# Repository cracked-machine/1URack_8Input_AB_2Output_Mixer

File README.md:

# 1URack_8Input_AB_2Output_Mixer
Eurorack-compatible 1U 8-channel mixer with selectable A/B outputs. 

<a href="https://www.instagram.com/p/BnoBRM4nUFm/?utm_source=ig_web_copy_link">Link to demo video!</a>

Assembly Instructions:
======================

A. Resistors

1) 8 x 2K2 on all R_LEDX positions (**R_LED1** - **R_LED8**)
2) 8 x 10K on all R_ChannelAB_OAin_RinX positions (**R_ChannelAB_OAin_Rin1** - **R_ChannelAB_OAin_Rin8**)
3) 2 x 10K on **R_ChanA_OAin_Rf1** and **R_ChanB_OAin_Rf1**
4) 2 x 22K on **R_ChanA_OAout_Rin1** and **R_ChanB_OAout_Rin1**
5) 2 x 1K  on **R_ChanA_OAout1** and **R_ChanB_OAout1** 

B. Capacitors

1) 2 x 100nF on **C_ChanA_POSBY1** and **C_ChanB_POSBY1**
2) 2 x 100nF on **C_ChanA_NEGBY1** and **C_ChanB_NEGBY1**
3) 1 x 100nF on **C_PW_BYNEG1**
4) 1 x 100nF on **C_PW_BYPOS1**

C. SOIC components

1) 2 x TL072 on **U_ChanA_OA1** and **U_ChanB_OA1**

D. ThroughHole Components

1) Solder one fader per section (1-8, A and B). Will only fit one way
2) Solder one Jack socket per section (1-8, A and B). Will only fit one way
3) solder one switch per input section (1-8). Orientation does not matter.
4) Solder pin headers in the power supply holes (2x5).

Troubleshooting:
================

1. Signal check:

Run a VCO signal into each of the inputs and check the signal at both outputs. You can use either an amplifier or an scope at the outputs. It can be helpful to draw a 2x8 grid for the inputs/outputs so you can mark each one in turn as you check.

If any of the inputs fail to produce a signal at an output then check that input section. If no signal appears at one of the output then check that output section. See below for further checks....

2. Visual Inspection:

Most problems will arise from bad solder joints on the SMT components so be sure to make a final visual inspection when done. 
You might find it easier to do this after cleaning the flux off the pcb first. If in doubt retouch the solder joint.

3. Electrical check:

Check for +/-12V voltages at the power supply pins. Also check pins 8 (positive) and 4 (negative) on the two SOIC TL072 OpAmps. 

Use a DMM to check the continuity between component pins.  

Check the resistance on pins connected to each resistor after soldering. If you get an open circuit reading then resolder the component.  Seeing a resistance value significantly less than marked, can be a sign that another component has bad solder joints.

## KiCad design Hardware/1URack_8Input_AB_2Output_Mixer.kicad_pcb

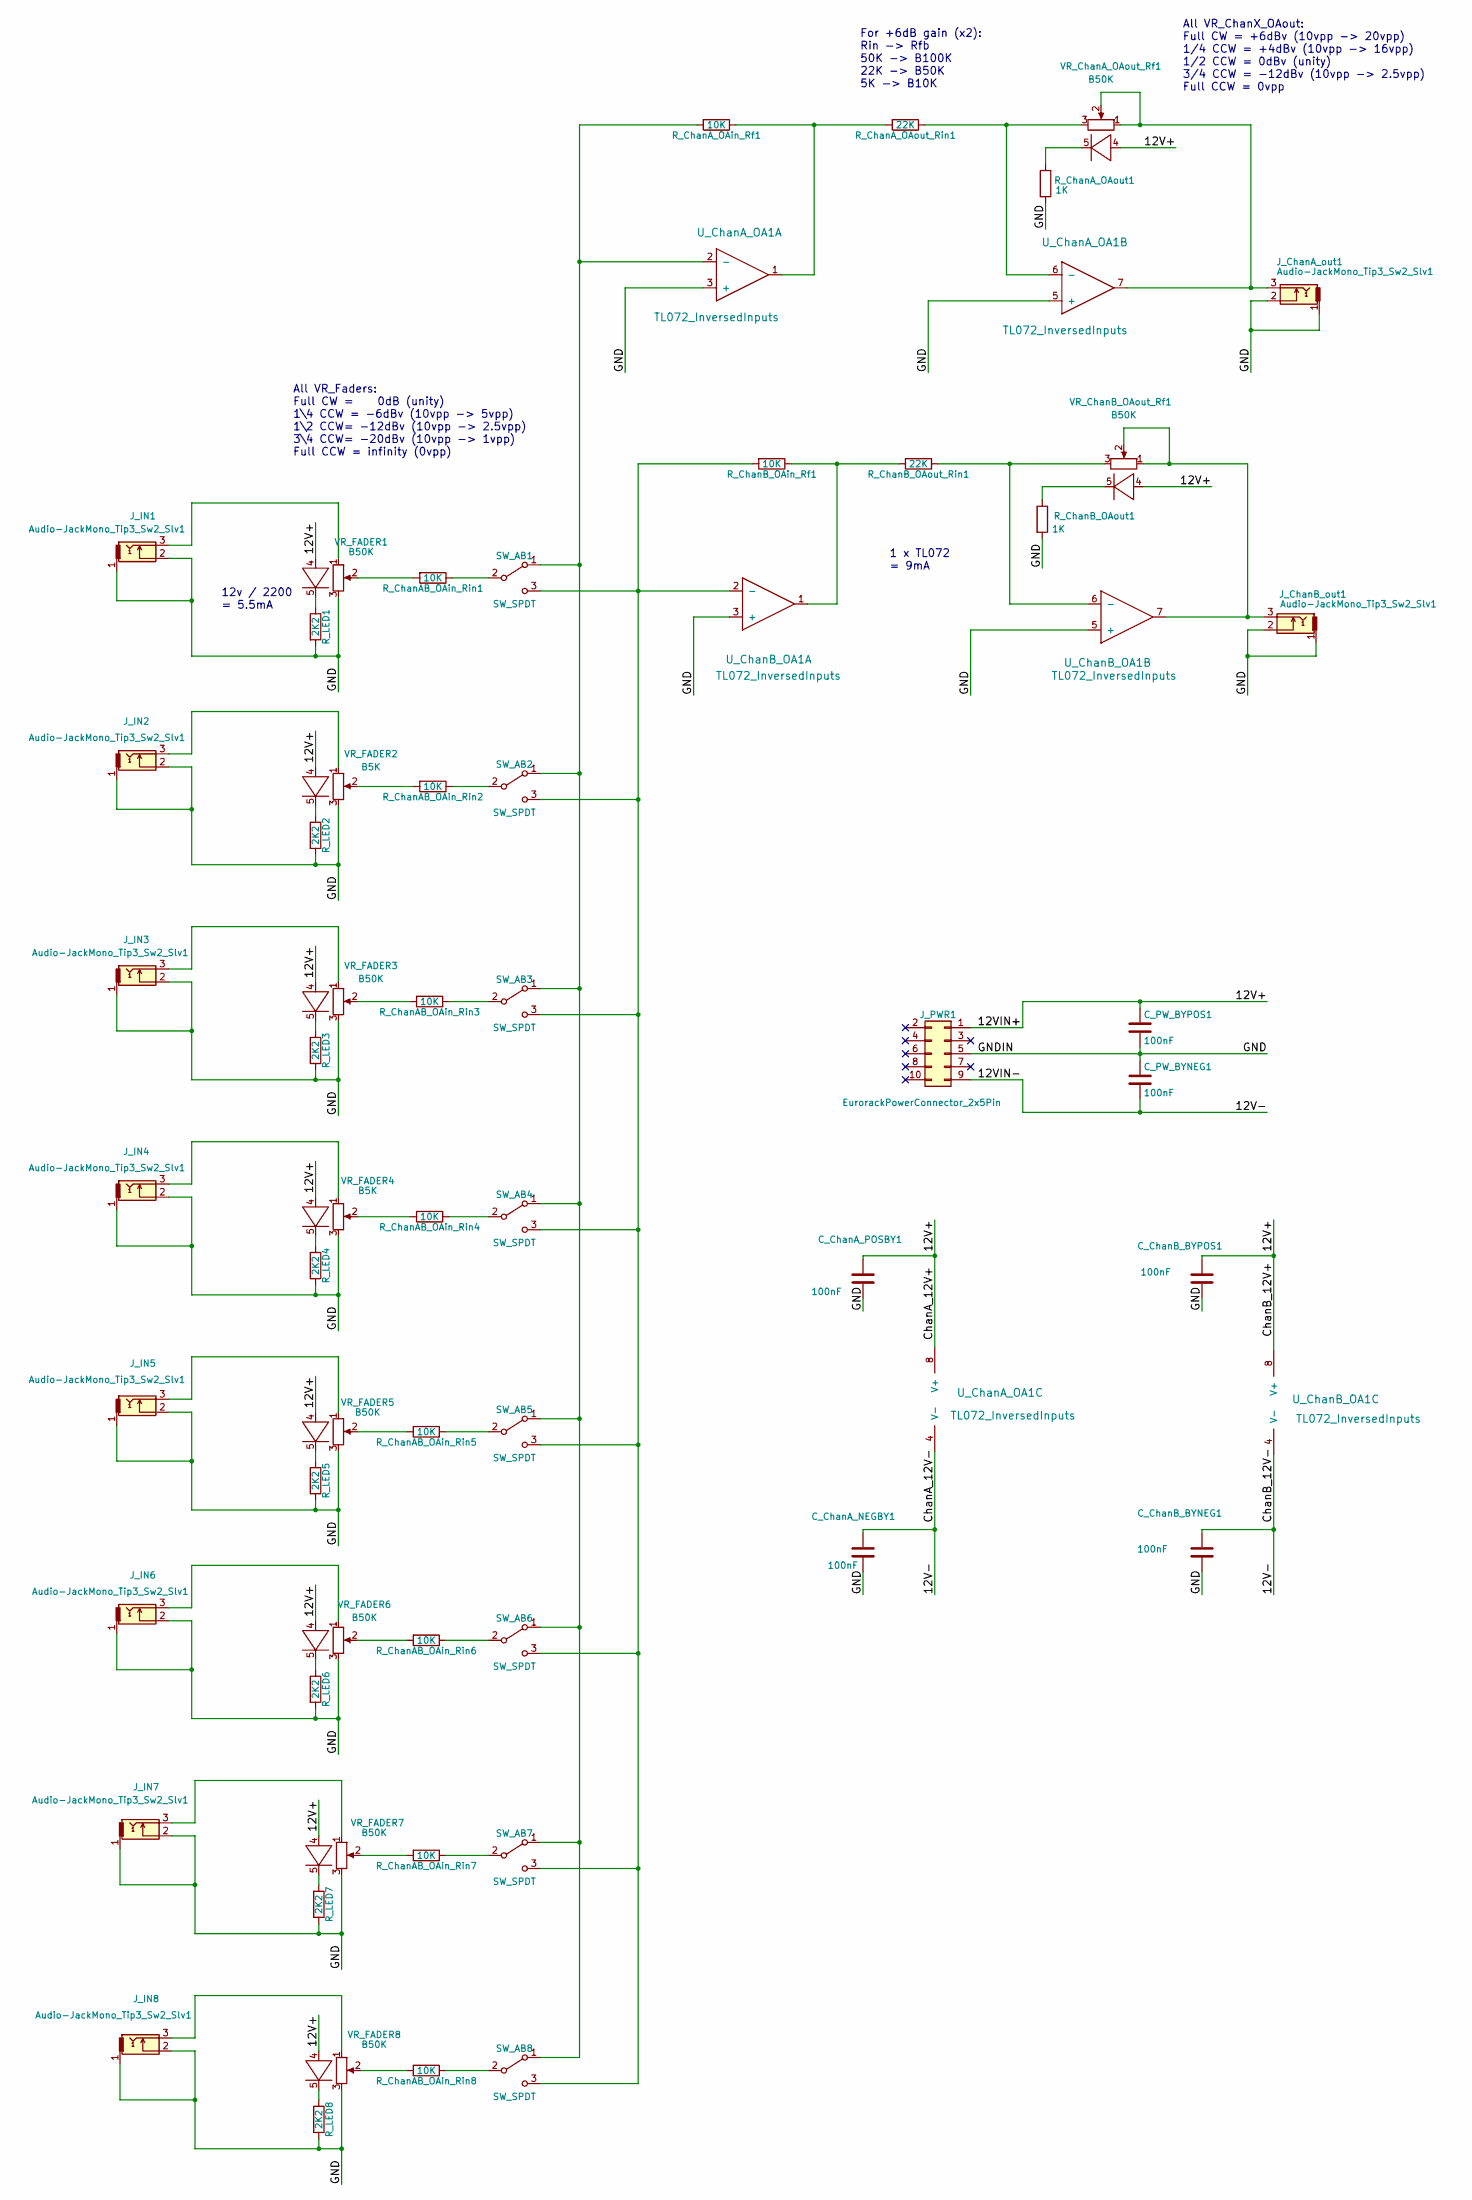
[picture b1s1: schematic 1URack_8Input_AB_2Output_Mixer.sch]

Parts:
C_ChanA_NEGBY1: 100nF; C_0805_HandSoldering
C_ChanA_POSBY1: 100nF; C_0805_HandSoldering
C_ChanB_BYNEG1: 100nF; C_0805_HandSoldering
C_ChanB_BYPOS1: 100nF; C_0805_HandSoldering
C_PW_BYNEG1: 100nF; C_0805_HandSoldering
C_PW_BYPOS1: 100nF; C_0805_HandSoldering
J_ChanA_out1: Audio-JackMono_Tip3_Sw2_Slv1; Conn_3.5mmJackMono_Vertical_PJ301M-12
J_ChanB_out1: Audio-JackMono_Tip3_Sw2_Slv1; Conn_3.5mmJackMono_Vertical_PJ301M-12
J_IN1, J_IN2, J_IN3, J_IN4, J_IN5, J_IN6, J_IN7, J_IN8: Audio-JackMono_Tip3_Sw2_Slv1; Conn_3.5mmJackMono_Vertical_PJ301M-12
J_PWR1: EurorackPowerConnector_2x5Pin; Pin_Header_Straight_2x05_Pitch2.54mm
R_ChanAB_OAin_Rin1, R_ChanAB_OAin_Rin2, R_ChanAB_OAin_Rin3, R_ChanAB_OAin_Rin4, R_ChanAB_OAin_Rin5, R_ChanAB_OAin_Rin6, R_ChanAB_OAin_Rin7, R_ChanAB_OAin_Rin8: 10K; R_0805_HandSoldering
R_ChanA_OAin_Rf1: 10K; R_0805_HandSoldering
R_ChanA_OAout1: 1K; R_0805_HandSoldering
R_ChanA_OAout_Rin1: 22K; R_0805_HandSoldering
R_ChanB_OAin_Rf1: 10K; R_0805_HandSoldering
R_ChanB_OAout1: 1K; R_0805_HandSoldering
R_ChanB_OAout_Rin1: 22K; R_0805_HandSoldering
R_LED1, R_LED2, R_LED3, R_LED4, R_LED5, R_LED6, R_LED7, R_LED8: 2K2; R_0805_HandSoldering
SW_AB1, SW_AB2, SW_AB3, SW_AB4, SW_AB5, SW_AB6, SW_AB7, SW_AB8: SW_SPDT; Dailywell_SPDT
U_ChanA_OA1: TL072_InversedInputs; SOIC-8-N
U_ChanB_OA1: TL072_InversedInputs; SOIC-8-N
VR_ChanA_OAout_Rf1: B50K; Slider_PTL20_LED_35MM
VR_ChanB_OAout_Rf1: B50K; Slider_PTL20_LED_35MM
VR_FADER1, VR_FADER3, VR_FADER5, VR_FADER6, VR_FADER7, VR_FADER8: B50K; Slider_PTL20_LED_35MM
VR_FADER2, VR_FADER4: B5K; Slider_PTL20_LED_35MM

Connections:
/12V+: C_ChanA_POSBY1.1, C_ChanB_BYPOS1.1, C_PW_BYPOS1.1, J_PWR1.1, U_ChanA_OA1.8 (V+), U_ChanB_OA1.8 (V+), VR_ChanA_OAout_Rf1.4, VR_ChanB_OAout_Rf1.4, VR_FADER1.4, VR_FADER2.4, VR_FADER3.4, VR_FADER4.4, VR_FADER5.4, VR_FADER6.4, VR_FADER7.4, VR_FADER8.4
/12V-: C_ChanA_NEGBY1.1, C_ChanB_BYNEG1.1, C_PW_BYNEG1.2, J_PWR1.9, U_ChanA_OA1.4 (V-), U_ChanB_OA1.4 (V-)
/GND: C_ChanA_NEGBY1.2, C_ChanA_POSBY1.2, C_ChanB_BYNEG1.2, C_ChanB_BYPOS1.2, C_PW_BYNEG1.1, C_PW_BYPOS1.2, J_ChanA_out1.1, J_ChanA_out1.2, J_ChanB_out1.1, J_ChanB_out1.2, J_IN1.1, J_IN1.2, J_IN2.1, J_IN2.2, J_IN3.1, J_IN3.2, J_IN4.1, J_IN4.2, J_IN5.1, J_IN5.2, J_IN6.1, J_IN6.2, J_IN7.1, J_IN7.2, J_IN8.1, J_IN8.2, J_PWR1.5, R_ChanA_OAout1.2, R_ChanB_OAout1.2, R_LED1.2, R_LED2.2, R_LED3.2, R_LED4.2, R_LED5.2, R_LED6.2, R_LED7.2, R_LED8.2, U_ChanA_OA1.3 (+), U_ChanA_OA1.5 (+), U_ChanB_OA1.3 (+), U_ChanB_OA1.5 (+), VR_FADER1.3, VR_FADER2.3, VR_FADER3.3, VR_FADER4.3, VR_FADER5.3, VR_FADER6.3, VR_FADER7.3, VR_FADER8.3
unnamed: J_ChanA_out1.3, U_ChanA_OA1.7, VR_ChanA_OAout_Rf1.1, VR_ChanA_OAout_Rf1.2
unnamed: J_ChanB_out1.3, U_ChanB_OA1.7, VR_ChanB_OAout_Rf1.1, VR_ChanB_OAout_Rf1.2
unnamed: J_IN1.3, VR_FADER1.1
unnamed: J_IN2.3, VR_FADER2.1
unnamed: J_IN3.3, VR_FADER3.1
unnamed: J_IN4.3, VR_FADER4.1
unnamed: J_IN5.3, VR_FADER5.1
unnamed: J_IN6.3, VR_FADER6.1
unnamed: J_IN7.3, VR_FADER7.1
unnamed: J_IN8.3, VR_FADER8.1
unnamed: R_ChanAB_OAin_Rin1.1, SW_AB1.2 (B)
unnamed: R_ChanAB_OAin_Rin1.2, VR_FADER1.2
unnamed: R_ChanAB_OAin_Rin2.1, SW_AB2.2 (B)
unnamed: R_ChanAB_OAin_Rin2.2, VR_FADER2.2
unnamed: R_ChanAB_OAin_Rin3.1, SW_AB3.2 (B)
unnamed: R_ChanAB_OAin_Rin3.2, VR_FADER3.2
unnamed: R_ChanAB_OAin_Rin4.1, SW_AB4.2 (B)
unnamed: R_ChanAB_OAin_Rin4.2, VR_FADER4.2
unnamed: R_ChanAB_OAin_Rin5.1, SW_AB5.2 (B)
unnamed: R_ChanAB_OAin_Rin5.2, VR_FADER5.2
unnamed: R_ChanAB_OAin_Rin6.1, SW_AB6.2 (B)
unnamed: R_ChanAB_OAin_Rin6.2, VR_FADER6.2
unnamed: R_ChanAB_OAin_Rin7.1, SW_AB7.2 (B)
unnamed: R_ChanAB_OAin_Rin7.2, VR_FADER7.2
unnamed: R_ChanAB_OAin_Rin8.1, SW_AB8.2 (B)
unnamed: R_ChanAB_OAin_Rin8.2, VR_FADER8.2
unnamed: R_ChanA_OAin_Rf1.1, R_ChanA_OAout_Rin1.2, U_ChanA_OA1.1
unnamed: R_ChanA_OAin_Rf1.2, SW_AB1.1 (A), SW_AB2.1 (A), SW_AB3.1 (A), SW_AB4.1 (A), SW_AB5.1 (A), SW_AB6.1 (A), SW_AB7.1 (A), SW_AB8.1 (A), U_ChanA_OA1.2 (-)
unnamed: R_ChanA_OAout1.1, VR_ChanA_OAout_Rf1.5
unnamed: R_ChanA_OAout_Rin1.1, U_ChanA_OA1.6 (-), VR_ChanA_OAout_Rf1.3
unnamed: R_ChanB_OAin_Rf1.1, R_ChanB_OAout_Rin1.2, U_ChanB_OA1.1
unnamed: R_ChanB_OAin_Rf1.2, SW_AB1.3 (C), SW_AB2.3 (C), SW_AB3.3 (C), SW_AB4.3 (C), SW_AB5.3 (C), SW_AB6.3 (C), SW_AB7.3 (C), SW_AB8.3 (C), U_ChanB_OA1.2 (-)
unnamed: R_ChanB_OAout1.1, VR_ChanB_OAout_Rf1.5
unnamed: R_ChanB_OAout_Rin1.1, U_ChanB_OA1.6 (-), VR_ChanB_OAout_Rf1.3
unnamed: R_LED1.1, VR_FADER1.5
unnamed: R_LED2.1, VR_FADER2.5
unnamed: R_LED3.1, VR_FADER3.5
unnamed: R_LED4.1, VR_FADER4.5
unnamed: R_LED5.1, VR_FADER5.5
unnamed: R_LED6.1, VR_FADER6.5
unnamed: R_LED7.1, VR_FADER7.5
unnamed: R_LED8.1, VR_FADER8.5

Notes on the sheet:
For +6dB gain (x2): Rin -> Rfb 50K -> B100K 22K -> B50K 5K -> B10K
All VR_ChanX_OAout: Full CW = +6dBv (10vpp -> 20vpp) 1/4 CCW = +4dBv (10vpp -> 16vpp) 1/2 CCW = 0dBv (unity) 3/4 CCW = -12dBv (10vpp -> 2.5vpp) Full CCW = 0vpp
All VR_Faders: Full CW = 0dB (unity) 1\4 CCW = -6dBv (10vpp -> 5vpp) 1\2 CCW= -12dBv (10vpp -> 2.5vpp) 3\4 CCW= -20dBv (10vpp -> 1vpp) Full CCW = infinity (0vpp)
12v / 2200 = 5.5mA
1 x TL072 = 9mA

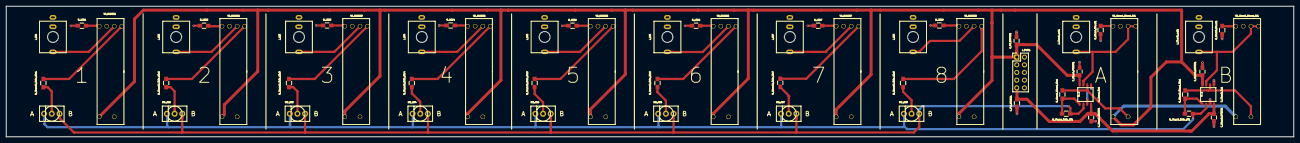
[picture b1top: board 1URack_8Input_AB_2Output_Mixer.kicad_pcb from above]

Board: 2 copper layers, 426.0 x 43.2 mm, 59 parts (0 on the bottom side), 45 nets.

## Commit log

2018-05-12 update
    - Recalculated gain values on opamps
2018-05-21 First draft board layout
2018-05-23 second draft
2018-05-24 third draft
2018-05-24 minor updates
2018-05-26 BOM update
2018-09-12 updated to Kicad 5
2018-09-12 save update
2018-10-02 Added front panel design
2018-10-10 Created Front Panel REVB
2018-10-17 Documentation corrections and restructure
